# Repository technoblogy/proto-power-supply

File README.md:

# Proto Power Supply
A portable breadboard-friendly adjustable power supply, designed as an ideal supply for Arduino projects and other low-power circuits. For more information see: http://www.technoblogy.com/show?LBR

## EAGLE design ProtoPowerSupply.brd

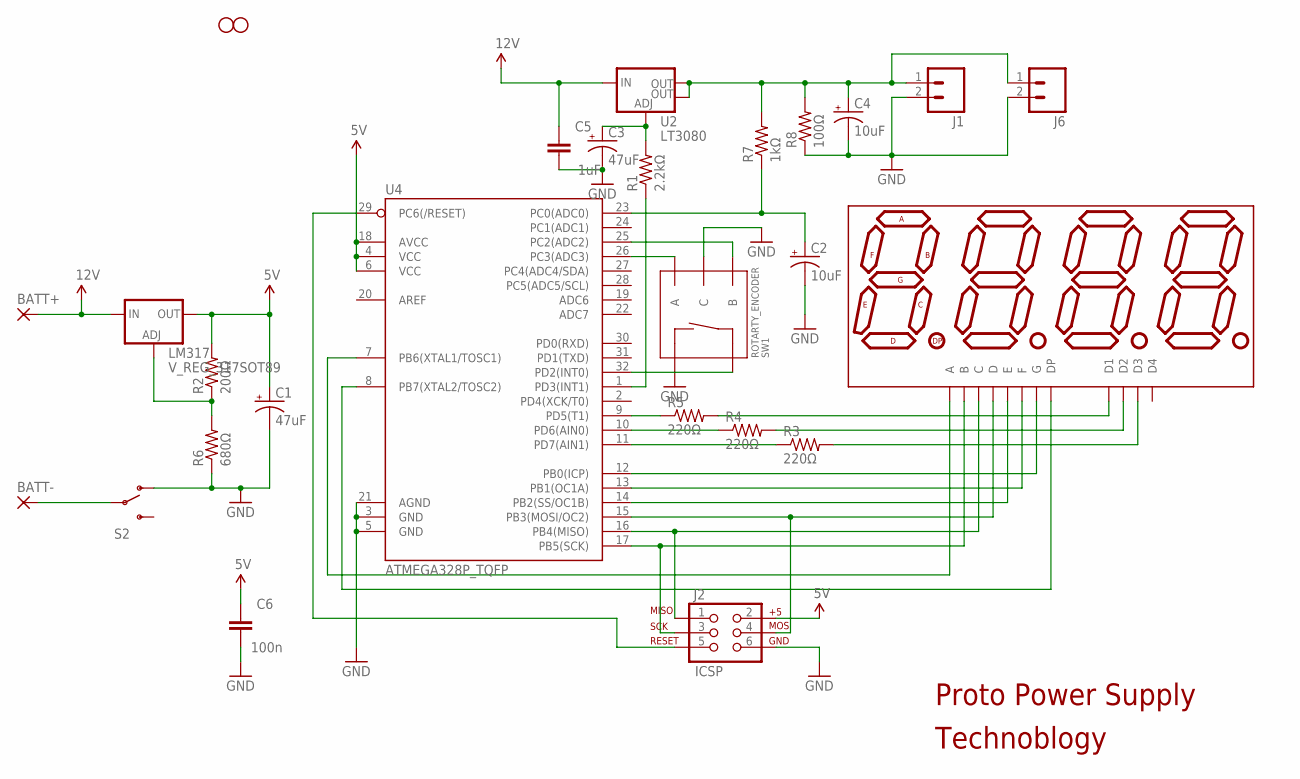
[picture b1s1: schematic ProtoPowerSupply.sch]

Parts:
BATT+: 1,6/0,9
BATT-: 1,6/0,9
C1, C3: 47uF; CPOL-RADIAL-10UF-25V
C2, C4: 10uF; CPOL-RADIAL-10UF-25V
C5: 1uF; 0603-CAP
C6: 100n; 0603-CAP
DISP1: KYX-2381
J1, J6: M021X02_NO_SILK; 1X02_NO_SILK
J2: ICSP; 2X3
JP4, JP5: STAND-OFF
LM317: V_REG_317SOT89; SOT89
R1: 2.2kΩ; R0805
R2: 200Ω; R0805
R3, R4, R5: 220Ω; R0805
R6: 680Ω; R0805
R7: 1kΩ; R0805
R8: 100Ω; R0805
S2: SWITCH-SPDTPTH; SWITCH-SPDT
SW1: ROTARTY_ENCODER; ROTARY_ENC_PLAIN
U2: LT3080; SOT223
U4: ATMEGA328P_TQFP; TQFP32-08

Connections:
5V: C1.1 (+), C6.1, J2.2, LM317.2 (OUT), R2.2, U4.4 (VCC), U4.6 (VCC), U4.18 (AVCC)
12V: BATT+.1, C5.1, LM317.3 (IN), U2.3 (IN)
GND: C1.2 (-), C2.2 (-), C3.2 (-), C4.2 (-), C5.2, C6.2, J1.2, J2.6, J6.2, R6.1, R8.1, S2.1 (O), SW1.C, SW1.SW-, U4.3 (GND), U4.5 (GND), U4.21 (AGND)
unnamed: DISP1.5 (G), U4.12 (PB0(ICP))
unnamed: C2.1 (+), R7.1, U4.23 (PC0(ADC0))
unnamed: C3.1 (+), R1.2, U2.1 (ADJ)
unnamed: BATT-.1, S2.2
unnamed: DISP1.10 (F), U4.13 (PB1(OC1A))
unnamed: DISP1.1 (E), U4.14 (PB2(SS/OC1B))
unnamed: DISP1.2 (D), J2.4, U4.15 (PB3(MOSI/OC2))
unnamed: DISP1.4 (C), J2.1, U4.16 (PB4(MISO))
unnamed: DISP1.7 (B), J2.3, U4.17 (PB5(SCK))
unnamed: DISP1.11 (A), U4.7 (PB6(XTAL1/TOSC1))
unnamed: DISP1.12 (D1), R5.2
unnamed: DISP1.3 (DP), U4.8 (PB7(XTAL2/TOSC2))
unnamed: DISP1.9 (D2), R4.2
unnamed: DISP1.8 (D3), R3.2
unnamed: R5.1, U4.9 (PD5(T1))
unnamed: R4.1, U4.10 (PD6(AIN0))
unnamed: R3.1, U4.11 (PD7(AIN1))
unnamed: SW1.B, U4.25 (PC2(ADC2))
unnamed: SW1.SW+, U4.32 (PD2(INT0))
unnamed: SW1.A, U4.26 (PC3(ADC3))
unnamed: J2.5, U4.29 (PC6(/RESET))
unnamed: R1.1, U4.1 (PD3(INT1))
unnamed: C4.1 (+), J1.1, J6.1, R7.2, R8.2, U2.2 (OUT), U2.4 (OUT)
unnamed: LM317.1 (ADJ), R2.1, R6.2

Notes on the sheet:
Proto Power Supply
Technoblogy

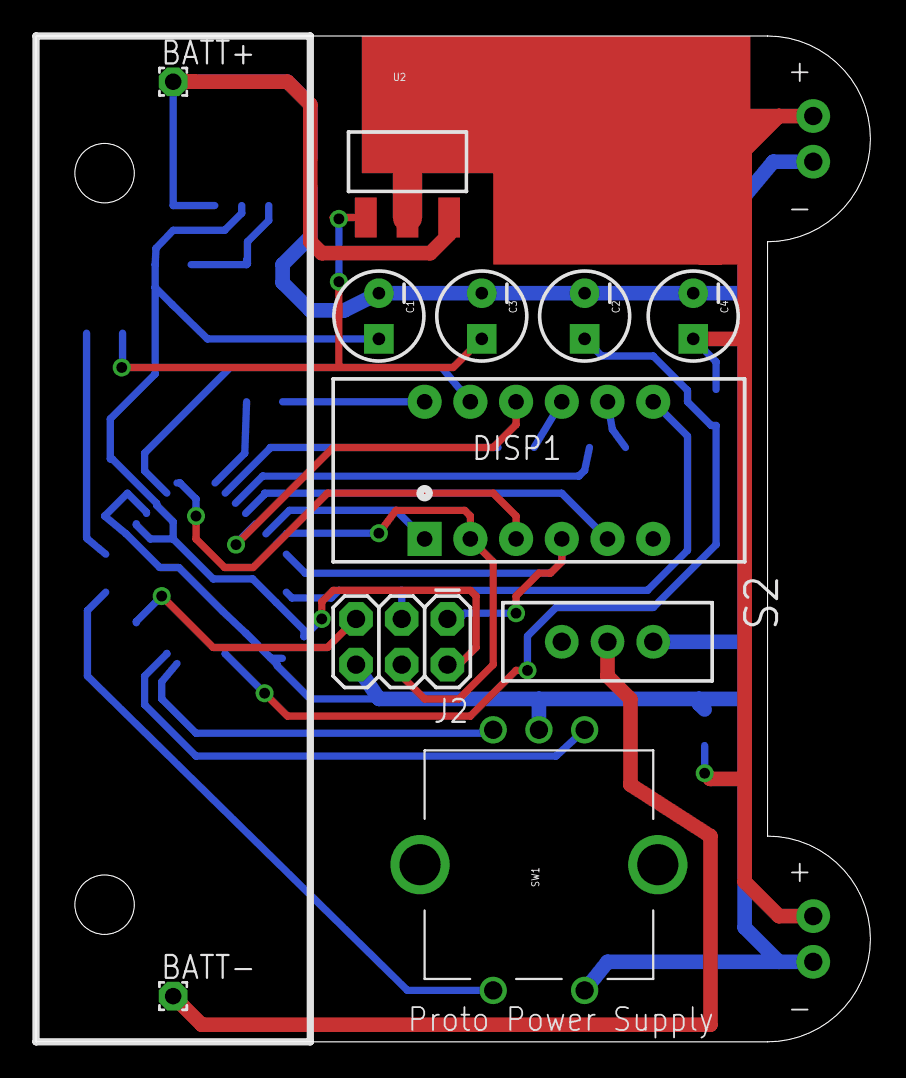
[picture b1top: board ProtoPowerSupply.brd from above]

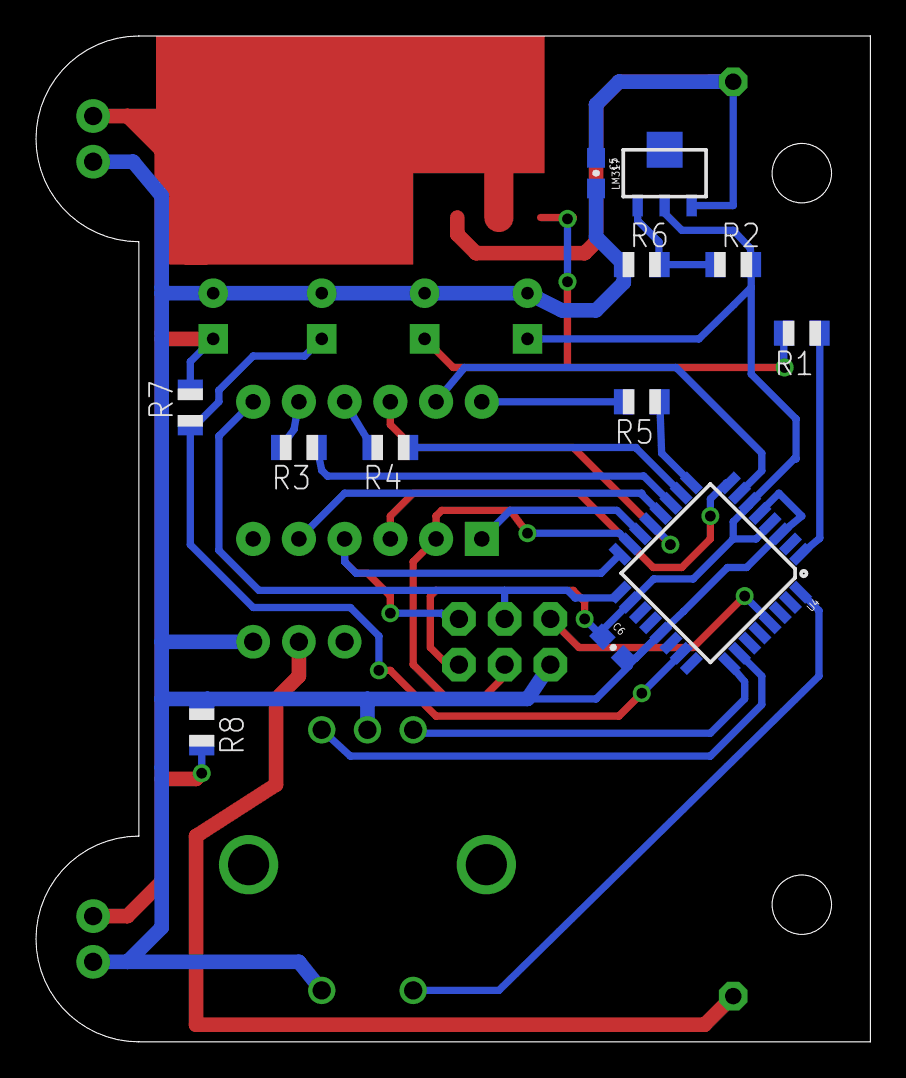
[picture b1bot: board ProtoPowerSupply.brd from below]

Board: 2 copper layers, 46.4 x 55.9 mm, 27 parts (12 on the bottom side), 27 nets.

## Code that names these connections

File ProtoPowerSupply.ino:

/* Proto Power Supply
 
   David Johnson-Davies - www.technoblogy.com - 4th November 2017
   ATmega328P @ 8 MHz (internal oscillator; BOD enabled (4.3V))
   
   CC BY 4.0
   Licensed under a Creative Commons Attribution 4.0 International license: 
   http://creativecommons.org/licenses/by/4.0/
*/

// Seven-segment definitions
const int charArrayLen = 12;
char charArray[charArrayLen] = {
//  ABCDEFG  Segments
  0b1111110, // 0
  0b0110000, // 1
  0b1101101, // 2
  0b1111001, // 3
  0b0110011, // 4
  0b1011011, // 5
  0b1011111, // 6
  0b1110000, // 7
  0b1111111, // 8
  0b1111011, // 9
  0b0000000, // 10  Space
  0b0000001  // 11  Dash
};

const int Dash = 11;
const int Space = 10;
const int Ndigits = 3;                 // Number of digits
const int Steps = 220;                 // Divide range into 220 steps of 0.025V
volatile int Count = 0;                // Encoder value goes from 0 to Steps-1

volatile int Buffer[] = { Dash, Dash, Dash };
volatile int digit = 0;

// Pin assignments; give the bit position in PORTD for each digit
int Digits[] = {5, 6, 7};

// All voltages are in mV
const int MaxVoltage = 5500;           // Maximum voltage; ie 5.50  V
const int Stepsize = 25;               // Stepsize; ie 0.025V
volatile int Voltage = 0;              // Current voltage setting
volatile int Target = 0;               // Target voltage for regulator
volatile bool Overload = false;        // Overload trip

// Set the PWM Voltage **********************************************

void SetVoltage (int Count) {
  Target = Count * Stepsize;
  OCR2B = Count;
}

// Rotary Encoder **********************************************

const int A = PINC2;
const int B = PINC3;

volatile int a0;
volatile int c0;

// Called when encoder value changes
void ChangeValue (bool Up) {
  Count = max(min((Count + (Up ? 1 : -1)), Steps-1), 0);
  SetVoltage(Count);
  Overload = false;
}

// Pin change interrupt service routine
ISR (PCINT1_vect) {
  int a = PINC>>A & 1;
  int b = PINC>>B & 1;
  if (a != a0) {              // A changed
    a0 = a;
    if (b != c0) {
      c0 = b;
      ChangeValue(a == b);
    }
  }
}

// Push button interrupt on INT0
ISR (INT0_vect) {
  Overload = true;
  SetVoltage(0);
  Count = 0;
}

// Display multiplexer **********************************************

void DisplayNextDigit() {
  static int LastVoltage;
  DDRD = DDRD & ~(1<<Digits[digit]);         // Make previous digit bit an input
  digit = (digit+1) % (Ndigits+1);
  if (digit < Ndigits) {
    char segs = charArray[Buffer[digit]];
    if (digit==0) segs = segs | 0x80;        // Decimal point
    PORTB = ~segs;
    DDRB = segs;
    DDRD = DDRD | 1<<Digits[digit];          // Make digit bit an output
    PORTD = PORTD | 1<<Digits[digit];        // Take digit bit high
  } else {
    DDRB = 0;                                // All segments off
    int Voltage = (ReadADC() * (long)MaxVoltage)/1024;
    // Add hysteresis to stop display jumping
    if (abs(LastVoltage - Voltage) >= 10) {
      LastVoltage = Voltage;
      // Overload protection - if output is more than 0.5V below target
      if (Target - Voltage > 500) {
        Overload = true;
        SetVoltage(0);
        Count = 0;
      }
      if (Overload) Buffer[0] = Buffer[1] = Buffer[2] = Dash;
      else Display(Voltage/10);
    }
  }
}

// Display a three digit decimal number
void Display (int i) {
  for (int d=2; d>=0 ; d--) {
    Buffer[d]=i % 10;
    i = i / 10;
  }
}

// Timer interrupt - multiplexes display and does ADC conversions
ISR (TIMER2_OVF_vect) {
  DisplayNextDigit();
}

// Do ADC conversion **********************************************

int ReadADC () {
  uint8_t low, high;
  ADCSRA = ADCSRA | 1<<ADSC;           // Start
  while (ADCSRA & 1<<ADSC);            // Wait while conversion in progress
  low = ADCL;
  high = ADCH;
  return high<<8 | low;
}

// Setup **********************************************

void setup() {
  DDRB = 0;                            // All segments off

  // Configure INT0 interrupt input (PD2)
  PORTD = 1<<PORTD2;                   // Set input pullup
  EICRA = 2<<ISC00;                    // Interrupt on falling edge
  EIMSK = 1<<INT0;                     // Enable interrupt
  
  // Configure rotary encoder input
  PORTC = 1<<PORTC2 | 1<<PORTC3;       // Set input pullups on A and B
  PCMSK1 = 1<<PCINT10;                 // Pin change interrupt on A (PC2/PCINT10)
  PCICR = 1<<PCIE1;                    // Enable interrupt
  PCIFR = 1<<PCIF1;                    // Clear interrupt flag
  
  // Set up Timer/Counter2 to generate PWM on OC2B (PD3) and multiplex the display
  DDRD = 1<<DDD3;                      // Make PD3 (OC2B) an output for PWM
  TCCR2A = 2<<COM2B0 | 1<<WGM20;       // Normal output, Phase Correct PWM to OCR2A
  TCCR2B = 1<<WGM22 | 2<<CS20;         // Divide clock by 8
  OCR2A = Steps-1;                     // Divide range into 220 steps of 0.025V
  TIMSK2 = 1<<TOIE2;                   // Enable overflow interrupt
  
  // Set up ADC on ADC0 (PC0)
  ADMUX = 1<<REFS0 | 0<<MUX0;          // Vcc as ref, ADC0 (PC0)
  ADCSRA = 1<<ADEN | 7<<ADPS0;         // Enable ADC, 62.5kHz clock
}

// Everything done under interrupt
void loop () {
}

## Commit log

2017-11-04 Version 1 - 4th November 2017
2018-04-02 Changed recommended fuse settings

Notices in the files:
parts and their libraries:
SparkFun-Capacitors: Licensing: Creative Commons ShareAlike 4.0 International - https://creativecommons.org/licenses/by-sa/4.0
SparkFun-Connectors: Licensing: CC v3.0 Share-Alike You are welcome to use this library for commercial purposes.
